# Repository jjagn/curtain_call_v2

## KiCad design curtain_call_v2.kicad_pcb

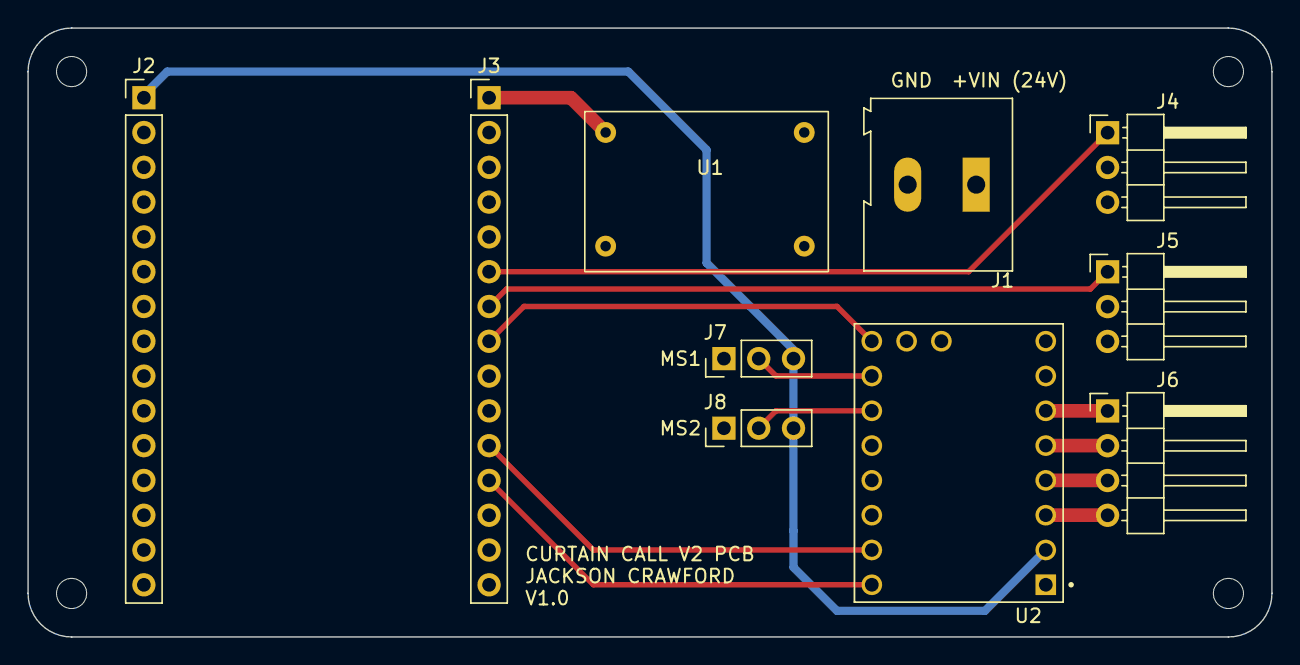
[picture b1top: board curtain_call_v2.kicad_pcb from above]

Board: 2 copper layers, 90.8 x 44.5 mm, 10 parts (0 on the bottom side), 15 nets.

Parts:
J1: Screw_Terminal_01x02; TerminalBlock_Altech_AK300-2_P5.00mm
J2, J3: Conn_01x15_Female; PinHeader_1x15_P2.54mm_Vertical
J4, J5: Conn_01x03_Male; PinHeader_1x03_P2.54mm_Horizontal
J6: Conn_01x04_Male; PinHeader_1x04_P2.54mm_Horizontal
J7, J8: Conn_01x03_Male; PinHeader_1x03_P2.54mm_Vertical
U1: SMALL_ALIEXPRESS_BUCK
U2: TMC2209_SILENTSTEPSTICK; MODULE_TMC2209_SILENTSTEPSTICK

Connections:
+3V3: J2.1, J7.3, J8.3, U2.2 (VIO)
+5V: J3.1, U1.4 (OUT+)
/DIR: J3.12, U2.9 (DIR)
/EN: J3.8, U2.16 (~EN)
/ENDSTOP_1: J3.6, J4.1
/ENDSTOP_2: J3.7, J5.1
/M1A: J6.3, U2.4 (M1A)
/M1B: J6.4, U2.3 (M1B)
/M2A: J6.2, U2.5 (M2A)
/M2B: J6.1, U2.6 (M2B)
/MS1: J7.2, U2.15 (MS1)
/MS2: J8.2, U2.14 (MS2)
/STEP: J3.11, U2.10 (STEP)
GND: J1.2, J2.2, J3.2, J4.2, J5.2, J7.1, J8.1, U1.2 (IN-), U1.3 (OUT-), U2.1 (GND), U2.7 (GND)
VCC: J1.1, U1.1 (IN+), U2.8 (VM)

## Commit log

2024-05-19 about halfway through schematic
2024-05-25 finished
2024-06-12 added esphome yaml code
